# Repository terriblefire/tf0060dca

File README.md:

# TF0060DCA

Drop-in replacement for the Taito TC0060DCA custom dual digitally-controlled
attenuator (as used on the Operation Wolf sound board, Taito schematic
W5100215A). Two LM1972 digital attenuators driven from the original 8-bit
parallel volume bus by a CH32V203C8T6 RISC-V MCU, with a measured calibration
mapping.

The primary aim of this project was to give me repro modules for my Operation 
Wolf machine but I also passed the measured curves on to MAME where they have 
been integrated. 

## Community

Questions, build reports and general chat: [join the Discord](https://discord.gg/awMzHfB86T).

## The repro matches the original

The key result of this project: measured on the [test fixture](testfixture/),
the TF0060DCA repro reproduces the original TC0060DCA's volume response to
within about 2% across the working range. Both sweeps below were taken at the
same drive level and are referenced to their full-volume (SD 255) output; the
x-axis is the machine's SD bus convention (0 = silence, 255 = full volume).
Where the curves part company at the bottom is just the two measurement runs'
differing noise floors.

Source data: [raw_curve_second_measure.csv](measured/raw_curve_second_measure.csv)
(original), [ch32_measured.csv](measured/ch32_measured.csv) (repro).

**Firmware response.** The repro's curve is fully explained by its firmware:
the computed line is derived from the `lm1972_mapping` table in
[main.c](firmware/CH32V203C8T6/User/main.c) and the LM1972 datasheet
attenuation values (SNAS094D Table 1): SD codes 0-86 map to LM1972 mute
(codes >= 0x7F = 100 dB), SD 87 gives -74.5 dB, SD 88 -44.5 dB, rising to
-4.5 dB at SD 255. The measured CH32 sweep matches it within about 2%
everywhere above the rig's ~ -23 dB noise floor, which hides the mute region.

## Test fixture

The fixture that produced the measurements: a Raspberry Pi Zero drives the SD
volume bus and clocks while the DUT's audio output is measured. It carries two
20-pin SIP sockets so an original TC0060DCA and the TF0060DCA replacement can
be exercised side by side.

| | |
|---|---|
|  |  |
| *Bare fixture: Molex power in, Pi Zero header, two SIP-20 sockets* | *TF0060DCA replacement modules* |
|  |  |
| *On the bench, mounted on a Pi Zero* | *With a device under test fitted* |
|  |  |
| *Probing during a measurement run* | *Overhead: Pi Zero and fixture* |

## TC0060DCA pin 7 (V_B)

Pin 7 of the original TC0060DCA has been asked about; the evidence from the
original hardware and this project:

- **Original Taito schematic** (W5100215A, sheet 4-2, IC49): pin 7 is strapped
  directly to the same ground rail as pins 6, 10 and 20. There is no external
  bias network (no capacitor or divider). Pin 8 is drawn as an unconnected
  stub (N.C.).
- **Test fixture**: a real TC0060DCA runs correctly with pin 7 tied to GND —
  the measured response above was captured that way.
- **This replacement** leaves pin 7 unconnected (net `V_B`) and pin 8 N.C.,
  and functions in the host board.

So pin 7 is a ground-referenced bias/substrate connection ("V_B"), tied to 0 V
in the machine and carrying no signal; a replacement can safely leave it
unconnected. It is not a volume or audio pin.

## Design notes (FAQ)

**Are C8-C11, C14 and C15 polarized?** No. They are drawn with Eagle's `C-US`
device, whose American-style symbol has one straight and one curved plate for
*any* capacitor - a polarized cap in Eagle carries an explicit "+" mark, which
these don't have. Physically they are 0805 ceramic (MLCC) parts, inherently
non-polar, used as AC coupling in the audio path.

**Volume conventions.** The machine's SD bus counts up (0 = silence, 255 =
full volume). The LM1972 register counts the other way (datasheet SNAS094D
Table 1: code 0x00 = 0.0 dB, 0.5 dB/step to 47.5 dB at code 95, 1.0 dB/step
to 78 dB at code 126, codes 0x7F-0xFF = 100 dB mute). The firmware's
`lm1972_mapping` table translates between the two. The legacy
[measured/measured.csv](measured/measured.csv) is indexed by attenuation
step (0 = full volume), not by SD code.

**What value are the coupling caps?** These are AC couplers, so the exact
value is not critical - it only sets the high-pass corner, which sits far
below audio for anything in this region. The design value was a nominal 6 uF;
on the JLCPCB production run the part matcher resolved this to a 10 uF X5R
(Samsung CL21A106KOQNNNE, LCSC C1713), which is what is fitted on assembled
boards and what the schematic now records. If hand-building, 4.7 uF, 6.8 uF
or 10 uF are all fine.

- `eagle/` - EAGLE schematic/board plus CAM, BOM/CPL and check tooling
  (`make help` for targets; gerbers and PDF build via the terriblefire78
  Docker images)
- `firmware/` - CH32V203 firmware (builds in `terriblefire78/mrs:latest`,
  or `make firmware` from the repo root)
- `testfixture/` - EAGLE test fixture board
- `measured/` - measured attenuation data and calibration table generator
- `gerbers/` - manufactured revisions (JLCPCB)

## License

Copyright (c) 2026 Stephen Leary (TerribleFire).

This design and its firmware are licensed under
[Creative Commons Attribution 4.0 International](LICENSE) (CC BY 4.0): you may
use, modify, manufacture and sell derivatives for any purpose, provided you
credit the original design and work.

WCH vendor sources under `firmware/` (Nanjing Qinheng Microelectronics) retain
their own copyright notices.

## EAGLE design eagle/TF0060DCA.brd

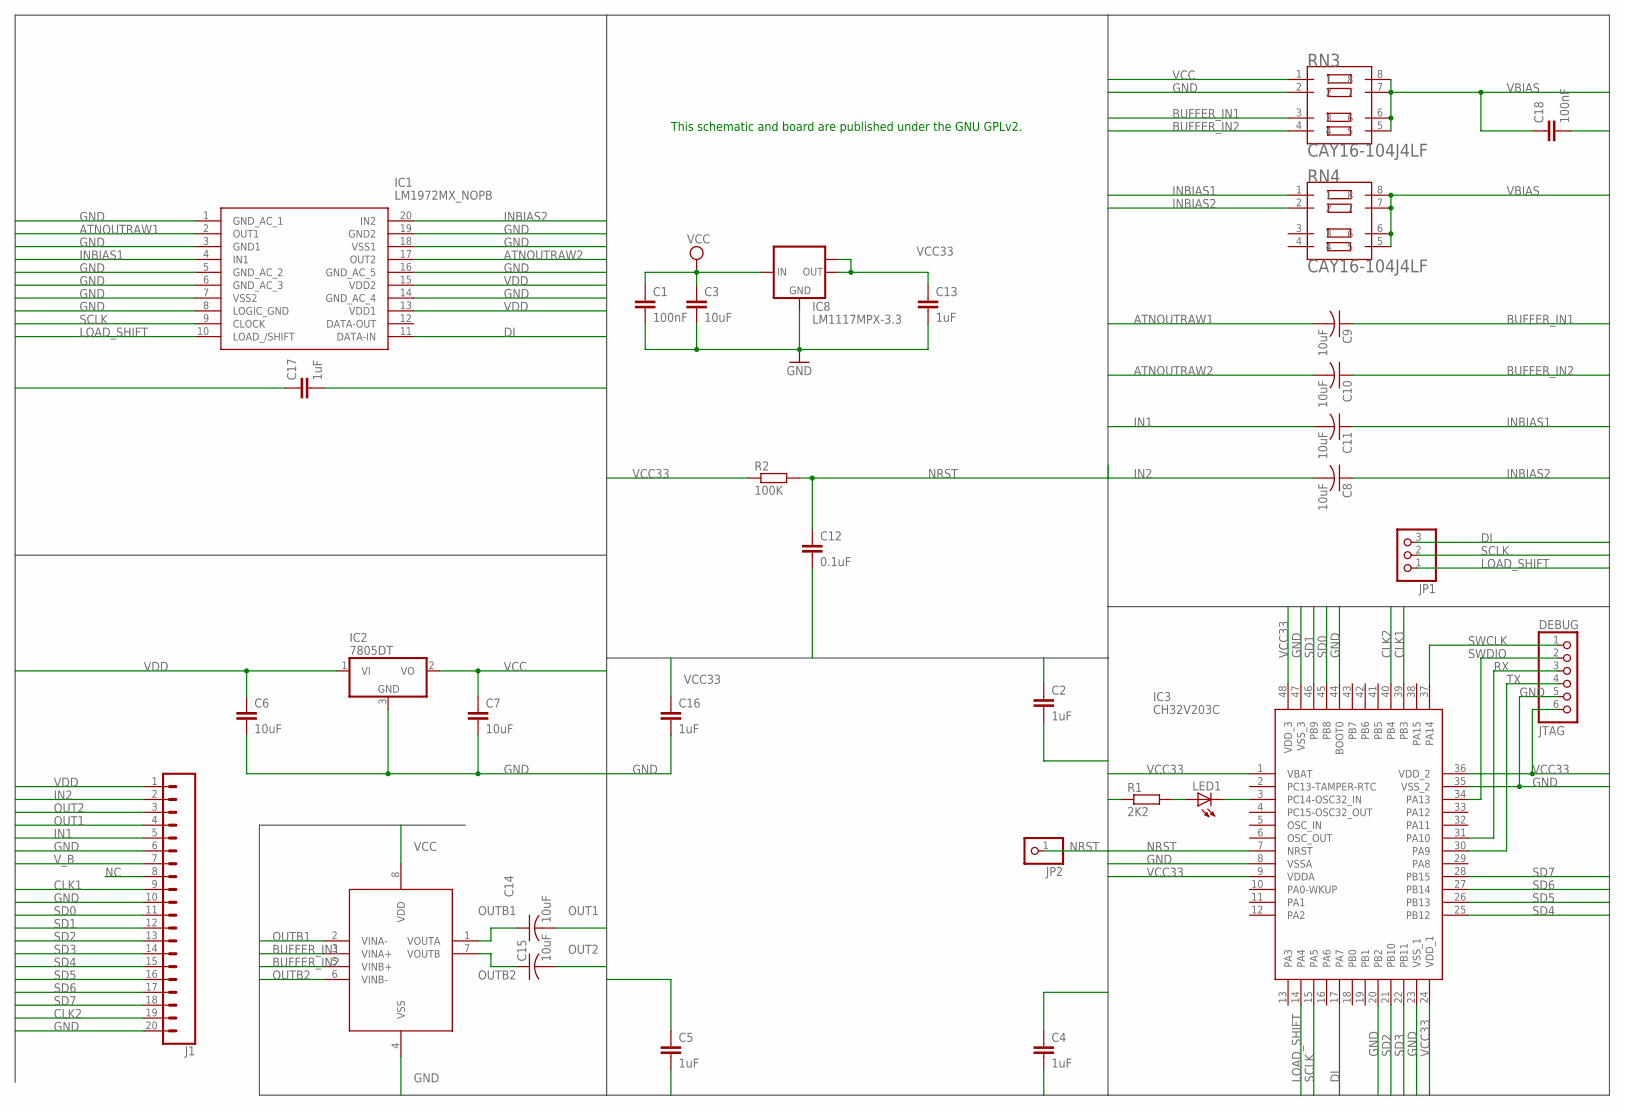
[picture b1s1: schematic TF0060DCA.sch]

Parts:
C1: 100nF; C1206
C2, C4, C5, C16, C17: 1uF; C0603
C3: 10uF; C0603
C6, C7: 10uF; C1206
C8, C9, C10, C11, C14, C15: 10uF; C0805
C12: 0.1uF; C0603
C13: 1uF; C1206
C18: 100nF; C0603
DEBUG: JTAG; 1X06_ROUND
IC1: LM1972MX_NOPB; SOIC127P1030X265-20N
IC2: 7805DT; TO252
IC3: CH32V203C; QFP50P900X900X160-48N
IC8: LM1117MPX-3.3; SOT223
IC12: MCP6002T-I_SN; SOIC127P600X175-8N
J1: CONN_20; 1X20
JP1: PINHD-1X3; 1X03
JP2: PINHD-1X1; 1X01
LED1: LEDCHIPLED_0603; CHIPLED_0603
R1: 2K2; R0603
R2: 100K; R0603
RN3, RN4: CAY16-104J4LF; RESCAXE80P320X160-8N

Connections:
ATNOUTRAW1: C9.2, IC1.2 (OUT1)
ATNOUTRAW2: C10.2, IC1.17 (OUT2)
BUFFER_IN1: C9.1, IC12.3 (VINA+), RN3.3
BUFFER_IN2: C10.1, IC12.5 (VINB+), RN3.4
CLK1: IC3.39 (PB3), J1.9
CLK2: IC3.40 (PB4), J1.19
DI: IC1.11 (DATA-IN), IC3.17 (PA7), JP1.3
GND: C1.2, C2.2, C3.2, C4.2, C5.2, C6.2, C7.2, C12.2, C13.2, C16.2, C17.2, C18.2, DEBUG.5, IC1.1 (GND_AC_1), IC1.3 (GND1), IC1.5 (GND_AC_2), IC1.6 (GND_AC_3), IC1.7 (VSS2), IC1.8 (LOGIC_GND), IC1.14 (GND_AC_4), IC1.16 (GND_AC_5), IC1.18 (VSS1), IC1.19 (GND2), IC2.3 (GND), IC3.8 (VSSA), IC3.20 (PB2), IC3.23 (VSS_1), IC3.35 (VSS_2), IC3.44 (BOOT0), IC3.47 (VSS_3), IC8.1 (GND), IC12.4 (VSS), J1.6, J1.10, J1.20, RN3.2
IN1: C11.2, J1.5
IN2: C8.2, J1.2
INBIAS1: C11.1, IC1.4 (IN1), RN4.1
INBIAS2: C8.1, IC1.20 (IN2), RN4.2
LOAD_SHIFT: IC1.10 (LOAD_/SHIFT), IC3.14 (PA4), JP1.1
unnamed: IC3.3 (PC14-OSC32_IN), LED1.C
unnamed: LED1.A, R1.2
NC: J1.8
NRST: C12.1, IC3.7 (NRST), JP2.1, R2.2
OUT1: C14.2, J1.4
OUT2: C15.2, J1.3
OUTB1: C14.1, IC12.1 (VOUTA), IC12.2 (VINA-)
OUTB2: C15.1, IC12.6 (VINB-), IC12.7 (VOUTB)
RX: DEBUG.3, IC3.31 (PA10)
SCLK: IC1.9 (CLOCK), IC3.15 (PA5), JP1.2
SD0: IC3.45 (PB8), J1.11
SD1: IC3.46 (PB9), J1.12
SD2: IC3.21 (PB10), J1.13
SD3: IC3.22 (PB11), J1.14
SD4: IC3.25 (PB12), J1.15
SD5: IC3.26 (PB13), J1.16
SD6: IC3.27 (PB14), J1.17
SD7: IC3.28 (PB15), J1.18
SWCLK: DEBUG.1, IC3.37 (PA14)
SWDIO: DEBUG.2, IC3.34 (PA13)
TX: DEBUG.4, IC3.30 (PA9)
VBIAS: C18.1, RN3.5, RN3.6, RN3.7, RN3.8, RN4.5, RN4.6, RN4.7, RN4.8
VCC: C1.1, C3.1, C7.1, C17.1, IC2.2 (VO), IC8.3 (IN), IC12.8 (VDD), RN3.1
VCC33: C2.1, C4.1, C5.1, C13.1, C16.1, DEBUG.6, IC3.1 (VBAT), IC3.9 (VDDA), IC3.24 (VDD_1), IC3.36 (VDD_2), IC3.48 (VDD_3), IC8.2 (OUT), IC8.TAB (OUT1), R1.1, R2.1
VDD: C6.1, IC1.13 (VDD1), IC1.15 (VDD2), IC2.1 (VI), J1.1
V_B: J1.7

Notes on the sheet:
This schematic and board are published under the GNU GPLv2.

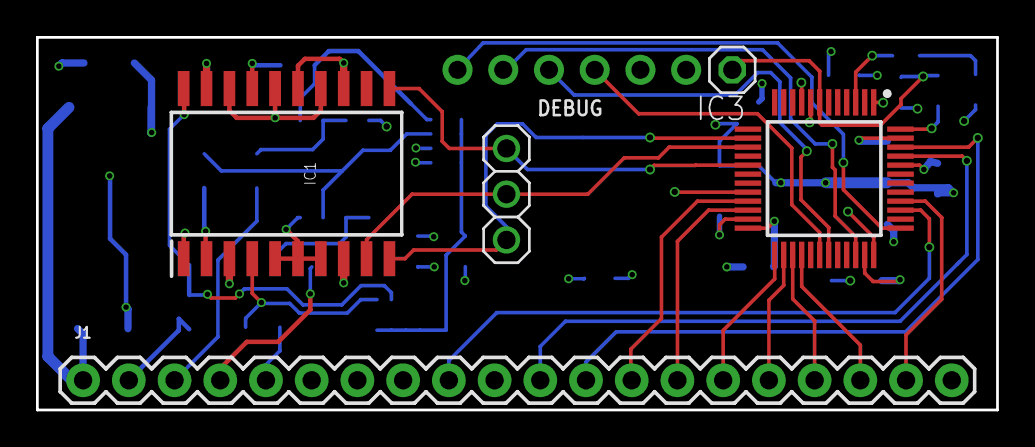
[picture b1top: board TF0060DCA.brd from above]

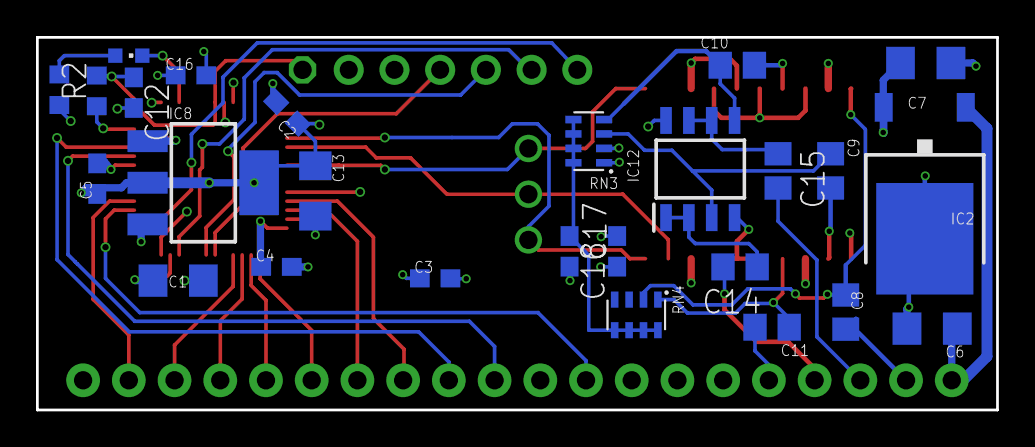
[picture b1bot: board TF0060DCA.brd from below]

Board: 4 copper layers, 53.3 x 20.7 mm, 32 parts (26 on the bottom side), 37 nets.

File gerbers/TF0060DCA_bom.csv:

Comment,Designator,Footprint,LCSC Part #
,JP2,1X01,
,JP1,1X03,
,J1,1X20,
,LED1,CHIPLED_0603,
0.1uF,C12,C0603,
1uF,C2 C4 C5 C16 C17,C0603,
1uF,C13,C1206,
2K2,R1,R0603,
6uF,C8 C9 C10 C11 C14 C15,C0805,
10uF,C3,C0603,
10uF,C6 C7,C1206,
100K,R2,R0603,
100nF,C18,C0603,
100nF,C1,C1206,
7805DT,IC2,TO252,
CAY16-104J4LF,RN3 RN4,RESCAXE80P320X160-8N,
CH32V203C,IC3,QFP50P900X900X160-48N,
JTAG,DEBUG,1X06_ROUND,
LM1117MPX-3.3,IC8,SOT223,
LM1972MX_NOPB,IC1,SOIC127P1030X265-20N,
MCP6002T-I_SN,IC12,SOIC127P600X175-8N,

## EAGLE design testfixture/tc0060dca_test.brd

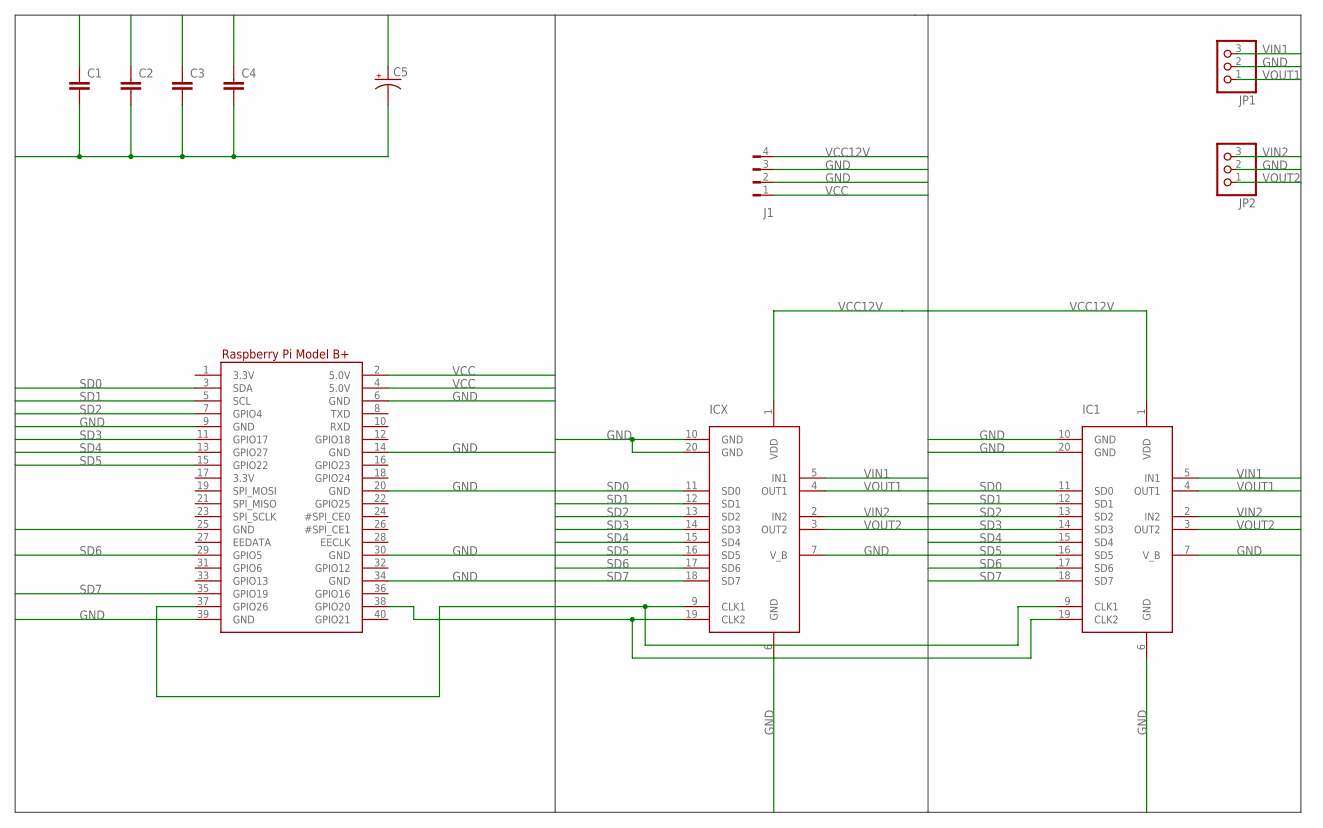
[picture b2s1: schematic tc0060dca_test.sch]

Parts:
C1, C2, C3, C4: CC1206; C1206
C5: CPOL-USTT5D9; TT5D9
IC1: TC0060DCA; 1X20
ICX: TC0060DCA; 1X20
J1: FLOP-4W; FLOP-4V
JP1, JP2: PINHD-1X3; 1X03
RPI1: RASPBERRYPI_BPLUS_IDC; 2X20

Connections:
GND: C1.2, C2.2, C3.2, C4.2, C5.-, IC1.6 (GND), IC1.7 (V_B), IC1.10 (GND), IC1.20 (GND), ICX.6 (GND), ICX.7 (V_B), ICX.10 (GND), ICX.20 (GND), J1.2, J1.3, JP1.2, JP2.2, RPI1.6 (GND), RPI1.9 (GND), RPI1.14 (GND), RPI1.20 (GND), RPI1.25 (GND), RPI1.30 (GND), RPI1.34 (GND), RPI1.39 (GND)
unnamed: IC1.9 (CLK1), ICX.9 (CLK1), RPI1.37 (GPIO26)
unnamed: IC1.19 (CLK2), ICX.19 (CLK2), RPI1.38 (GPIO20)
SD0: IC1.11 (SD0), ICX.11 (SD0), RPI1.3 (SDA)
SD1: IC1.12 (SD1), ICX.12 (SD1), RPI1.5 (SCL)
SD2: IC1.13 (SD2), ICX.13 (SD2), RPI1.7 (GPIO4)
SD3: IC1.14 (SD3), ICX.14 (SD3), RPI1.11 (GPIO17)
SD4: IC1.15 (SD4), ICX.15 (SD4), RPI1.13 (GPIO27)
SD5: IC1.16 (SD5), ICX.16 (SD5), RPI1.15 (GPIO22)
SD6: IC1.17 (SD6), ICX.17 (SD6), RPI1.29 (GPIO5)
SD7: IC1.18 (SD7), ICX.18 (SD7), RPI1.35 (GPIO19)
VCC: C1.1, C2.1, C3.1, J1.1, RPI1.2 (5.0V), RPI1.4 (5.0V)
VCC12V: C4.1, C5.+, IC1.1 (VDD), ICX.1 (VDD), J1.4
VIN1: IC1.5 (IN1), ICX.5 (IN1), JP1.3
VIN2: IC1.2 (IN2), ICX.2 (IN2), JP2.3
VOUT1: IC1.4 (OUT1), ICX.4 (OUT1), JP1.1
VOUT2: IC1.3 (OUT2), ICX.3 (OUT2), JP2.1

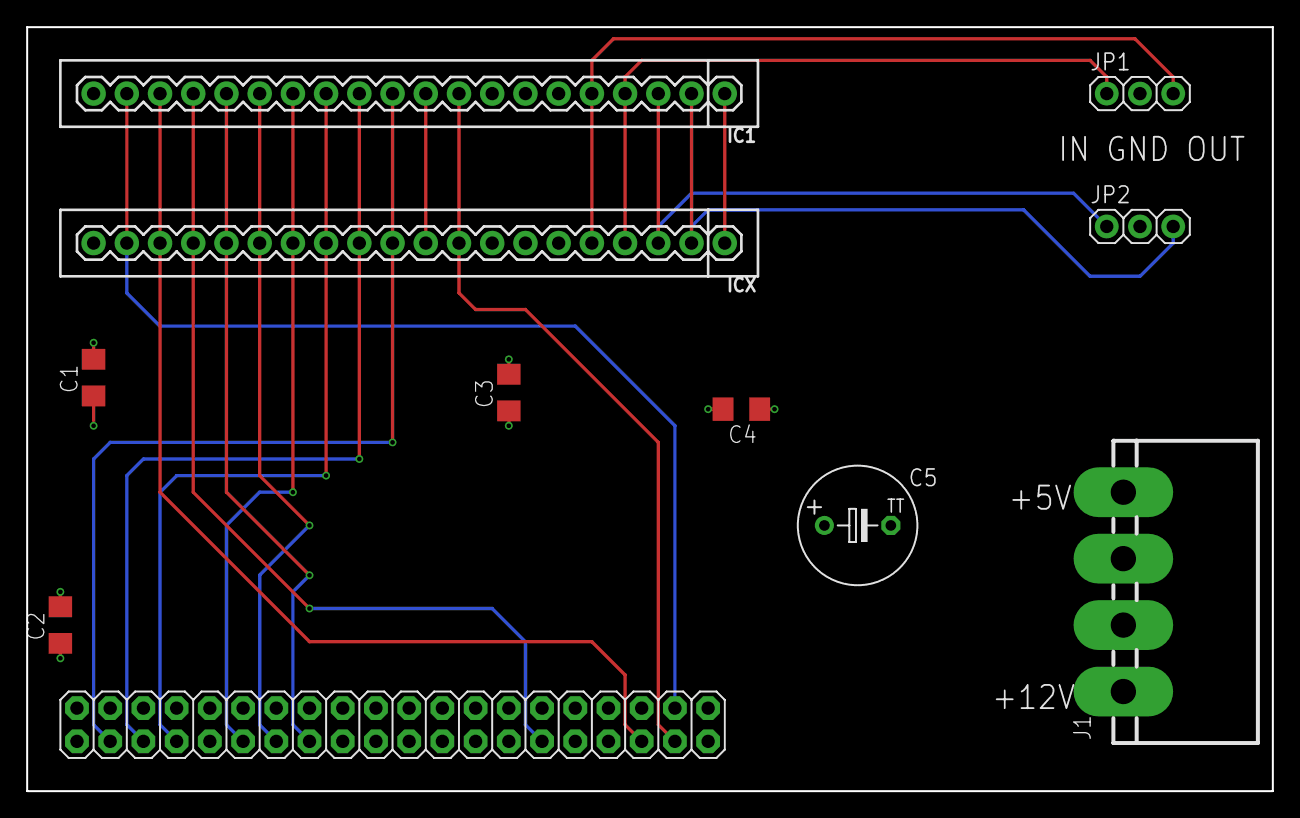
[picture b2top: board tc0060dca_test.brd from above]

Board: 4 copper layers, 95.2 x 58.4 mm, 11 parts (0 on the bottom side), 17 nets.

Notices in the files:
parts and their libraries:
SparkFun-Connectors: Licensing: Creative Commons ShareAlike 4.0 International - https://creativecommons.org/licenses/by-sa/4.0
microbuilder: This work is placed in the public domain, and may be freely used for commercial and non-commercial work with the following conditions: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
